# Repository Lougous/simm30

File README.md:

# simm30
* 30 pins DRAM memory module, 4Mi x 8bits
* No parity
* Such a pain to solder

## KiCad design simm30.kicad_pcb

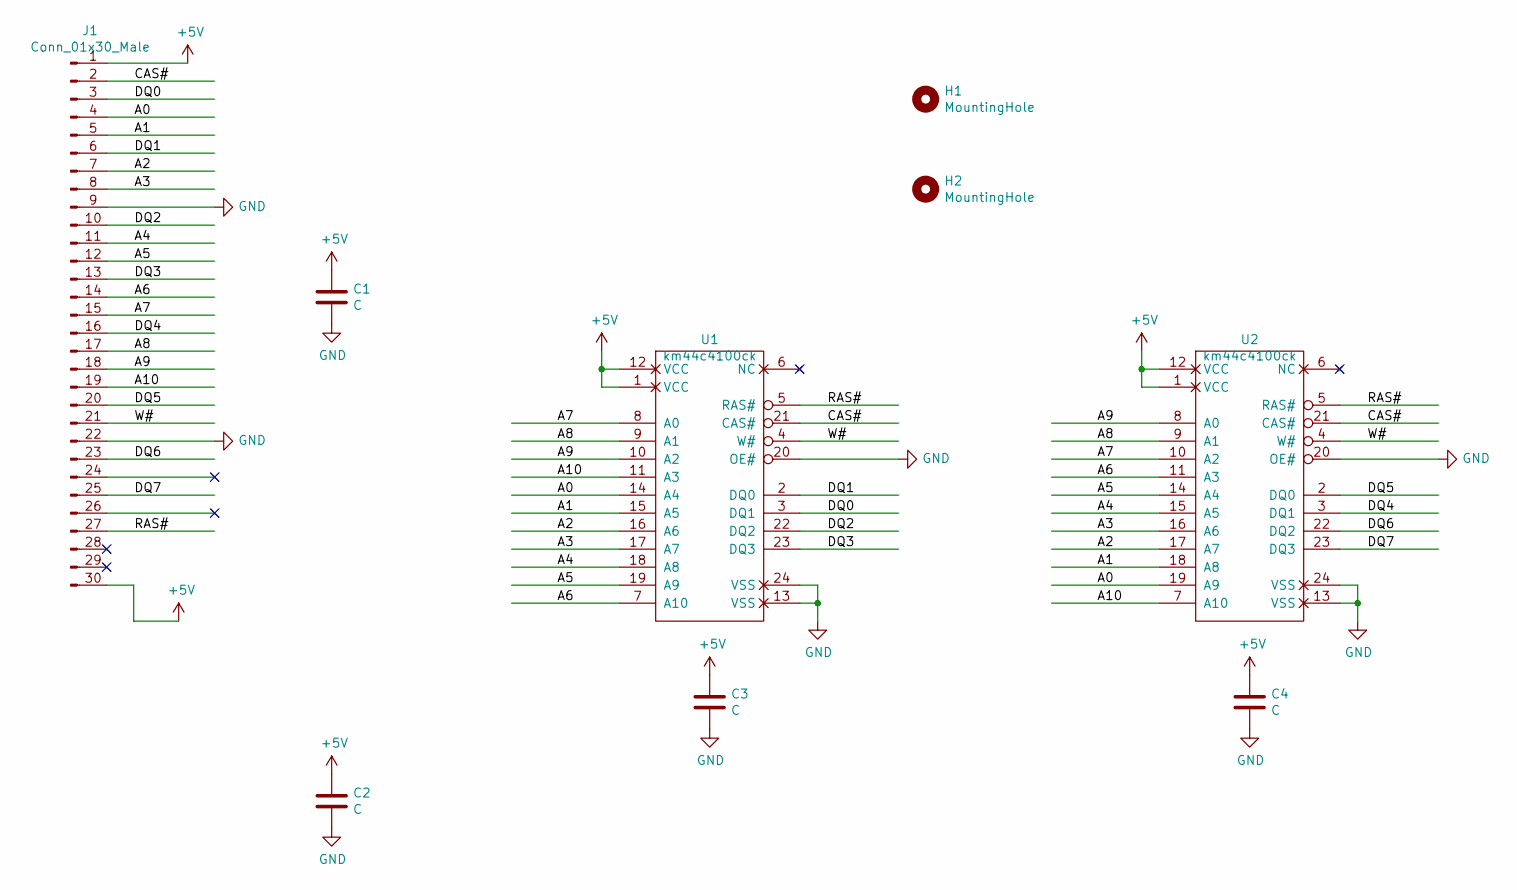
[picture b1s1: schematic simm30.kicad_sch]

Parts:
C1, C2, C3, C4: C; C_0805_HandSoldering
H1, H2: MountingHole; MountingHole_3.2mm_M3_ISO14580
J1: Conn_01x30_Male; simm30
U1, U2: km44c4100ck; DRAM-SOJ-24

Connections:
+5V: C1.1, C2.1, C3.1, C4.1, J1.1, J1.30, U1.1 (VCC), U1.12 (VCC), U2.1 (VCC), U2.12 (VCC)
/A0: J1.4, U1.14 (A4), U2.19 (A9)
/A1: J1.5, U1.15 (A5), U2.18 (A8)
/A2: J1.7, U1.16 (A6), U2.17 (A7)
/A3: J1.8, U1.17 (A7), U2.16 (A6)
/A4: J1.11, U1.18 (A8), U2.15 (A5)
/A5: J1.12, U1.19 (A9), U2.14 (A4)
/A6: J1.14, U1.7 (A10), U2.11 (A3)
/A7: J1.15, U1.8 (A0), U2.10 (A2)
/A8: J1.17, U1.9 (A1), U2.9 (A1)
/A9: J1.18, U1.10 (A2), U2.8 (A0)
/A10: J1.19, U1.11 (A3), U2.7 (A10)
/CAS#: J1.2, U1.21 (CAS#), U2.21 (CAS#)
/DQ0: J1.3, U1.3 (DQ1)
/DQ1: J1.6, U1.2 (DQ0)
/DQ2: J1.10, U1.22 (DQ2)
/DQ3: J1.13, U1.23 (DQ3)
/DQ4: J1.16, U2.3 (DQ1)
/DQ5: J1.20, U2.2 (DQ0)
/DQ6: J1.23, U2.22 (DQ2)
/DQ7: J1.25, U2.23 (DQ3)
/RAS#: J1.27, U1.5 (RAS#), U2.5 (RAS#)
/W#: J1.21, U1.4 (W#), U2.4 (W#)
GND: C1.2, C2.2, C3.2, C4.2, J1.9, J1.22, U1.13 (VSS), U1.20 (OE#), U1.24 (VSS), U2.13 (VSS), U2.20 (OE#), U2.24 (VSS)

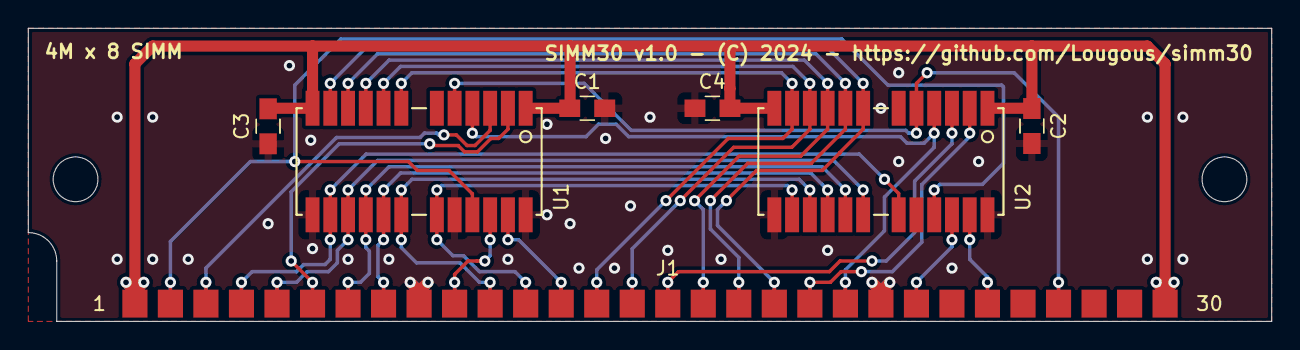
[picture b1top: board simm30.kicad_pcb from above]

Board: 2 copper layers, 88.9 x 21.0 mm, 9 parts (0 on the bottom side), 24 nets.

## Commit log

2024-07-26 import files

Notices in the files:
simm30.kicad_pcb:
SIMM30 v1.0 - (C) 2024 - https://github.com/Lougous/simm30
